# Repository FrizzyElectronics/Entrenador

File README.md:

# Entrenador
Entrenador básico para Arduino Micro

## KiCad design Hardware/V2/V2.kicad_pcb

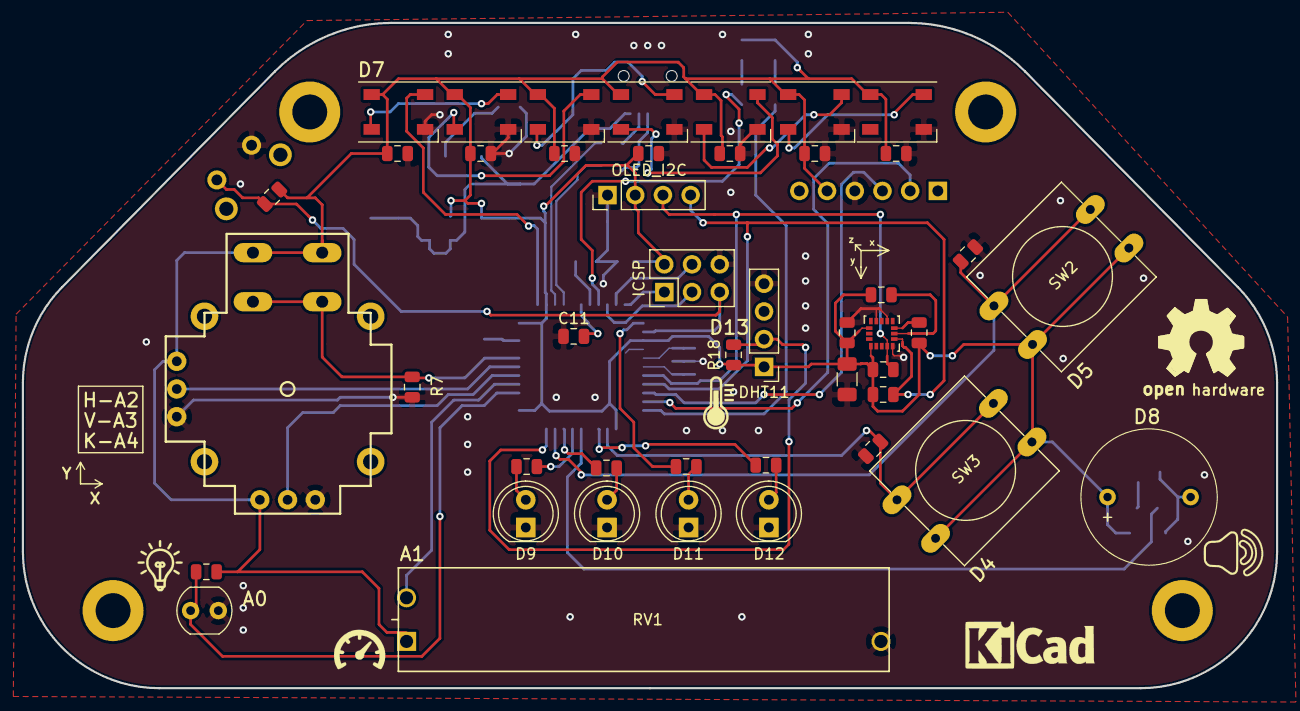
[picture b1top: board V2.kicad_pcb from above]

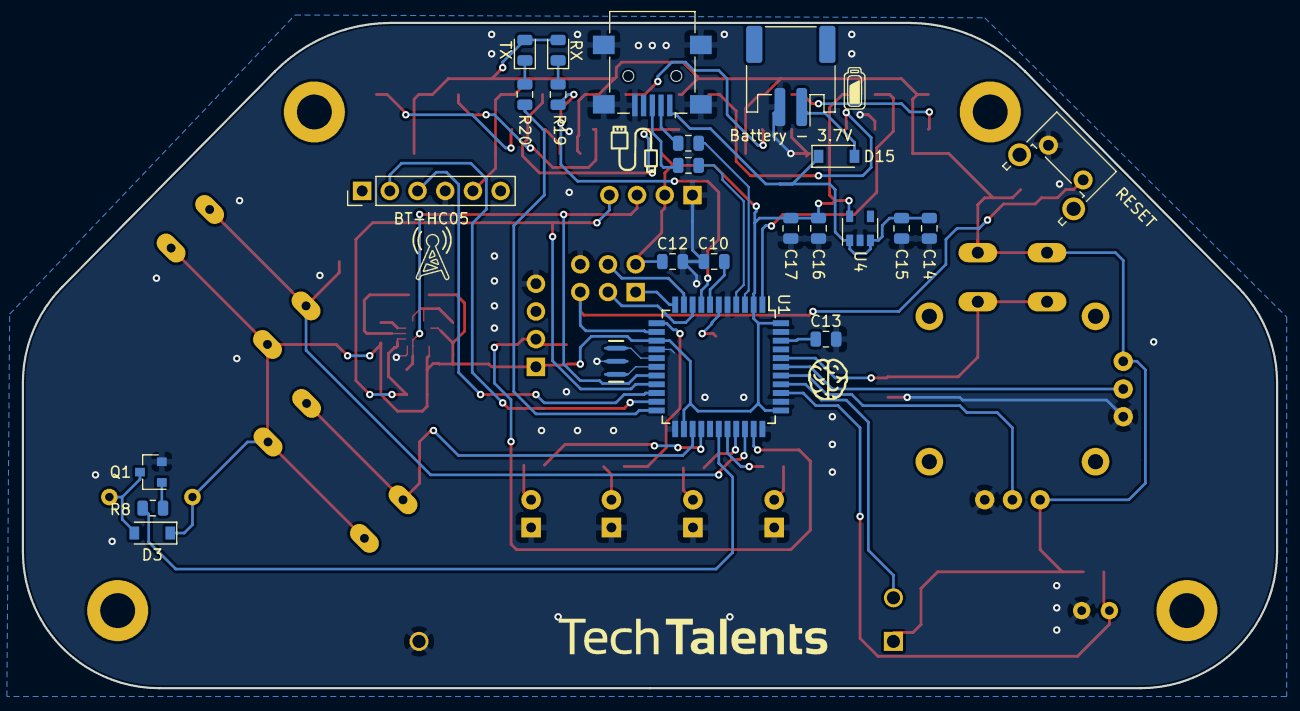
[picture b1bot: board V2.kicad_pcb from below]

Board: 2 copper layers, 115.0 x 61.0 mm, 69 parts (24 on the bottom side), 53 nets.

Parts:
BT-HC05: BT_CONN; PinHeader_1x06_P2.54mm_Vertical
BZ1: Buzzer; BUZZER-PB1240
Battery - 3.7V: BAT; JST_PH_S2B-PH-SM4-TB_1x02-1MP_P2.00mm_Horizontal
C1, C3, C4, C5, C6, C7, C8, C9: 100n; C_0805_2012Metric
C2: 10uF; C_1206_3216Metric
C10, C11, C12, C15, C16, C17: 1uF; C_0805_2012Metric
C13: 100nF; C_0805_2012Metric
C14: 10uF; C_0805_2012Metric
D1, D2, D4, D5, D6, D7, D12#2: WS2812B; LED_WS2812B_PLCC4_5.0x5.0mm_P3.2mm
D3, D15: 1N4148; D_SOD-123
D9: LED_Y; LED_D5.0mm
D10: LED_G; LED_D5.0mm
D11: LED_B; LED_D5.0mm
D12: LED_R; LED_D5.0mm
DHT11: DHT11; PinHeader_1x04_P2.54mm_Vertical
ICSP: ICSP; PinHeader_2x03_P2.54mm_Vertical
J1: USB_B_Mini; USB_Mini-B_Lumberg_2486_01_Horizontal
OLED_I2C: I2C_OLED; PinHeader_1x04_P2.54mm_Vertical
Q1: MMBT2222; SOT-23
R1, R2: 22R; R_0805_2012Metric
R3, R4, R18: 4k7; R_0805_2012Metric
R5, R6, R17: 10k; R_0805_2012Metric
R7, R11, R12: 10K; R_0805_2012Metric
R8: 100R; R_0805_2012Metric
R9: 100k; R_0805_2012Metric
R10: R_PHOTO; R_LDR_4.9x4.2mm_P2.54mm_Vertical
R13, R14, R15, R16: 220R; R_0805_2012Metric
R19, R20: 330; R_0805_2012Metric
RESET: SW_Push; SW_Tactile_SPST_Angled_PTS645Vx39-2LFS
RV1: 10k; Potentiometer_Techtalents
RX: RED; LED_0805_2012Metric
S1: JOYSTICK_THUMB; JOYSTICK
SW2, SW3: SW_Push; SW_PUSH-12mm
TX: GREEN; LED_0805_2012Metric
U1: ATmega32U4-AU; TQFP-44_10x10mm_P0.8mm
U2: LIS3DH; LGA-16_3x3mm_P0.5mm_LayoutBorder3x5y
U4: AP2112K-3.3; SOT-23-5
Y1: 16MHz; RESONATOR-SMD-3.2X1.3

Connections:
+3V3: BT-HC05.5, BZ1.1, C1.1, C2.1, C3.2, C4.2, C5.2, C6.2, C7.2, C8.2, C9.2, C12.1, C16.1, C17.1, D1.1, D2.1, D3.1, D4.1, D5.1, D6.1, D7.1, D12#2.1, DHT11.1, ICSP.2, OLED_I2C.2, R3.2, R4.2, R5.1, R6.1, R9.2, R17.2, R18.2, RV1.1, RX.2, S1.B1A, S1.H1, S1.V1, SW2.2, SW3.2, TX.2, U1.2, U1.14, U1.24, U1.34, U1.44, U2.1, U2.14, U4.5
BTN1: R12.2, SW3.1, U1.25
BTN2: R11.2, SW2.1, U1.31
BT_RX: BT-HC05.2, U1.21
BT_TX: BT-HC05.3, U1.20
BUZZ: R8.2, U1.28
D+: R1.1, U1.4
D-: R2.1, U1.3
DHT: DHT11.2, R18.1, U1.32
GND: BT-HC05.4, Battery - 3.7V.2, C1.2, C2.2, C3.1, C4.1, C5.1, C6.1, C7.1, C8.1, C9.1, C10.2, C11.1, C12.2, C13.2, C14.2, C15.2, C16.2, C17.2, D1.3, D2.3, D4.3, D5.3, D6.3, D7.3, D9.1, D10.1, D11.1, D12.1, D12#2.3, DHT11.4, ICSP.6, J1.5, J1.6, OLED_I2C.1, Q1.2, R7.1, R10.2, R11.1, R12.1, RESET.1, RV1.3, S1.H3, S1.V3, U1.5, U1.15, U1.23, U1.33, U1.35, U1.43, U2.5, U2.10, U2.12, U4.2, Y1.2
JOY-BTN: R7.2, S1.B2A, U1.40
JOY-H: S1.H2, U1.38
JOY-V: S1.V2, U1.39
LDR: R9.1, R10.1, U1.36
LED_B: R14.2, U1.12
LED_G: R16.2, U1.30
LED_R: R13.2, U1.26
LED_Y: R15.2, U1.29
MISO: ICSP.1, U1.11
MOSI: ICSP.4, U1.10
NEO: D1.4, U1.1
unnamed: BZ1.2, D3.2, Q1.3
unnamed: C10.1, U1.7
unnamed: C11.2, U1.6
unnamed: C13.1, U1.42
unnamed: D1.2, D2.4
unnamed: D2.2, D4.4
unnamed: D4.2, D5.4
unnamed: D5.2, D6.4
unnamed: D6.2, D7.4
unnamed: D12.2, R13.1
unnamed: D11.2, R14.1
unnamed: D9.2, R15.1
unnamed: D10.2, R16.1
unnamed: D7.2, D12#2.4
unnamed: R19.1, RX.1
unnamed: R20.1, TX.1
unnamed: Battery - 3.7V.1, D15.2
unnamed: J1.2, R2.2
unnamed: J1.3, R1.2
unnamed: Q1.1, R8.1
unnamed: R5.2, U2.8
unnamed: R6.2, U2.7
unnamed: R19.2, U1.8
unnamed: R20.2, U1.22
unnamed: U1.16, Y1.3
unnamed: U1.17, Y1.1
POT: RV1.2, U1.37
RST: ICSP.5, R17.1, RESET.2, U1.13
SCK: ICSP.3, U1.9
SCL: OLED_I2C.3, R3.1, U1.18, U2.4
SDA: OLED_I2C.4, R4.1, U1.19, U2.6
VUSB: C14.1, C15.1, D15.1, J1.1, U4.1, U4.3

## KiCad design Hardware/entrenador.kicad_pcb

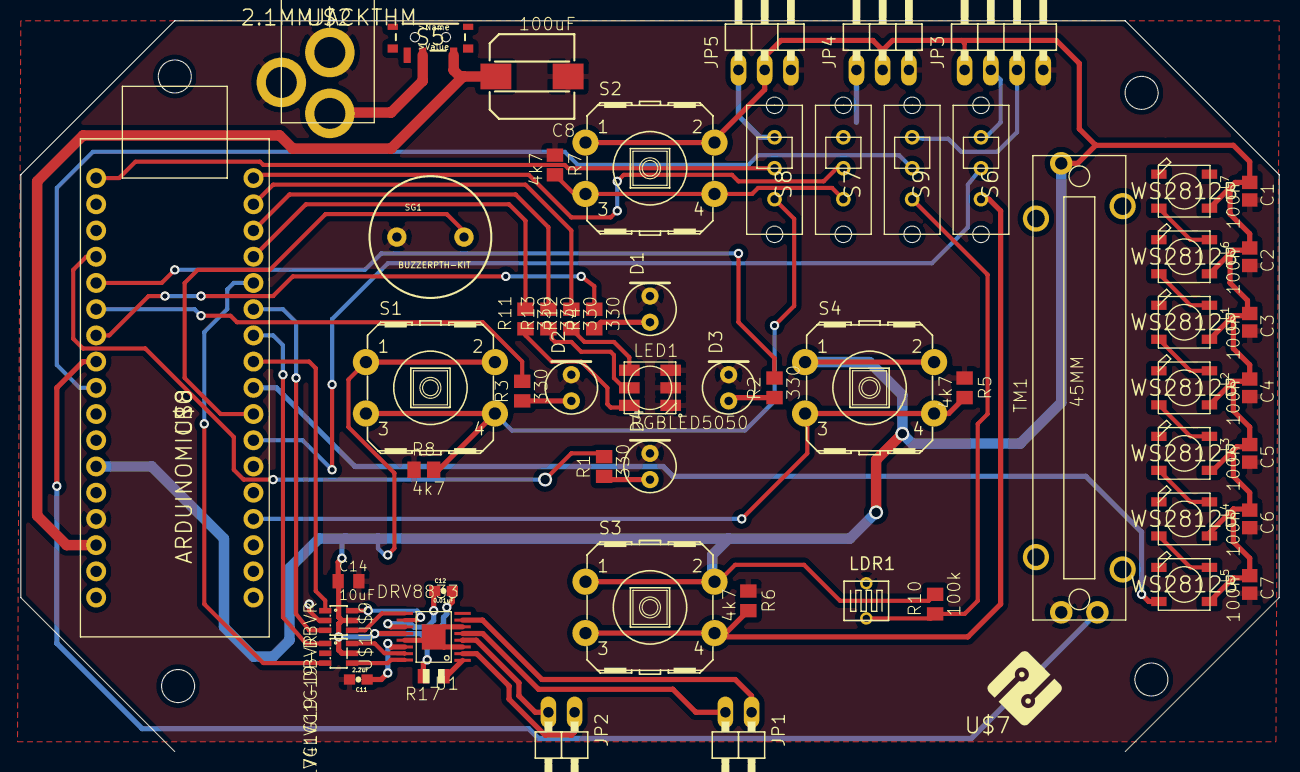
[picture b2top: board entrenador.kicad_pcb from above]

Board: 2 copper layers, 121.9 x 70.8 mm, 63 parts (0 on the bottom side), 48 nets.

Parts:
C1, C2, C3, C4, C5, C6, C7: 100n; C0805
C8: 100uF; 175TMP-0808
C11: 2.2uF; 0603-CAP
C12: 0.01uF; 0603-CAP
C14: 10uF; C0805K
D1, D2, D3, D4: LED5MM
JP1, JP2: 1X02/90
JP3: 1X04/90
JP4, JP5: 1X03/90
L1, L2, L3, L4, L5, L6, L7: WS2812B
LDR1: LDR338-54C
LED1: RGBLED5050
R1, R2, R3, R4, R11, R12, R13: 330; M0805
R5, R6, R7, R8: 4k7; M0805
R10: 100k; M0805
R17: R0805
S1, S2, S3, S4: B3F-40XX-ROUND
S5: SWITCH-SPST-SMD-A
S6, S7, S8, S9: SS-12F44G4
SG1: BUZZERPTH-KIT; BUZZER-12MM-KIT
TM1: SLIDEPOT-45
U1: DRV8833; PWP16
U$1, U$9: SN74LVC1G19SN74LVC1G19-DBVR; SOT23-6
U$2: 2.1MMJACKTHM; PJ-102A
U$3, U$4, U$5, U$6: 3,2
U$7: LOGO_BITS
U$8: ARDUINOMICRO

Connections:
!SLEEP: R17.1, U1.1
AIN1: U1.16, U$1.4
AIN2: U1.15, U$1.6
BIN1: U1.9, U$9.4
BIN2: U1.10, U$9.6
BUZZ: SG1.+, U$8.P$10
DIRA: U$1.3, U$8.P$5
DIRB: U$8.P$6, U$9.3
EXT2: S6.2, U$8.P$11
EXT3: S7.2, U$8.P$1
EXT4: S8.2, U$8.P$34
EXT5: S9.2, U$8.P$26
GND: C1.2, C2.2, C3.2, C4.2, C5.2, C6.2, C7.2, C8.-, C11.2, C14.2, D1.K, D2.K, D3.K, D4.K, JP3.4, JP4.3, JP5.3, LDR1.1, LED1.4, LED1.5, LED1.6, R5.1, R6.1, R7.1, R8.1, SG1.-, TM1.A, U1.0, U1.3, U1.6, U1.13, U$1.2, U$2.RING, U$8.P$12, U$8.P$21, U$9.2
LDR: LDR1.2, R10.1, S9.3
LED1: R1.2, U$8.P$31
LED2: R2.2, U$8.P$30
LED3: R3.2, U$8.P$29
LED4: R4.2, U$8.P$28
M1A: JP2.1, U1.2
M1B: JP2.2, U1.4
M2A: JP1.1, U1.7
M2B: JP1.2, U1.5
unnamed: JP3.2, S6.1
unnamed: JP3.3, S9.1
unnamed: D1.A, R4.1
unnamed: D2.A, R3.1
unnamed: D3.A, R2.1
unnamed: D4.A, R1.1
unnamed: JP4.1, S7.1
unnamed: LED1.3, R11.1
unnamed: LED1.1, R12.1
unnamed: LED1.2, R13.1
unnamed: C12.1, U1.11
unnamed: JP5.1, S8.1
unnamed: S5.2, U$2.TIP
unnamed: C11.1, U1.14
PB1: R5.2, S4.3, S4.4, U$8.P$14
PB2: R6.2, S3.3, S3.4, S6.3
PB3: R7.2, S2.3, S2.4, S7.3
PB4: R8.2, S1.3, S1.4, S8.3
PWMA: U$1.1, U$8.P$7
PWMB: U$8.P$8, U$9.1
RGB_B: R11.2, U$8.P$4
RGB_G: R12.2, U$8.P$2
RGB_R: R13.2, U$8.P$3
SLIDER: TM1.B, U$8.P$27
VCC: C1.1, C2.1, C3.1, C4.1, C5.1, C6.1, C7.1, C12.2, C14.1, JP3.1, JP4.2, JP5.2, R10.2, R17.2, S1.1, S1.2, S2.1, S2.2, S3.1, S3.2, S4.1, S4.2, TM1.C, U1.12, U$1.5, U$8.P$23, U$9.5
VIN: C8.+, S5.3, U$8.P$20

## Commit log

2016-07-02 Add The License
2016-07-02 Archivos añadidos
    Archivos añadidos
2016-07-02 Version mandada a fabrica
    Documentacion terminada.
2016-07-02 Entrenador Arduino Micro
2016-07-22 Entrenador para arduino micro
    Partlist generado.
2016-09-15 FALTA PONER LA SERIGRAFIA .Arreglados todos los issues del circuito salvo determinar por que los pines meten ruido.
2016-09-15 me falto revisar una cosa del anterior commit, disculpas. curregido
2016-09-20 Serigrafia TechTalents Añadida
2016-12-29 Mandada a fabrica
    Version 1.1
2016-12-29 Ultima version
2019-03-05 Árbol de carpetas cambiado
2019-03-05 Version 2 comenzada
2019-03-07 Acelerómetro añadido
2019-03-08 Cambiado a 3.3V
2019-03-08 Esquema terminado
2019-03-08 Esquema colocado
2019-03-19 Huellas asignadas
2019-03-19 Comenzando la placa
2019-03-20 Componentes colocados
2019-03-20 Enrutado comenzado
2019-03-21 Cambio de forma
2019-03-21 Placa enrutada
2019-03-22 Colocando lo componentes en 3D
2019-03-22 Trabajando en la serigrafía
2019-03-22 Guardado de seguridad
2019-03-26 Serigrafias añadidas
2019-03-26 DRC pasado
2019-03-29 Taladros del Slider ensanchados
2019-03-29 Zonas rellenadas
